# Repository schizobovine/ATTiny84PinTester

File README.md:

# ATTiny84PinTester
Hardware and firmware to test the ATTiny84 series of chips to make sure all GPIOs are working (i.e., I haven't fried them from ESD or a cat peeing on them or whatever).

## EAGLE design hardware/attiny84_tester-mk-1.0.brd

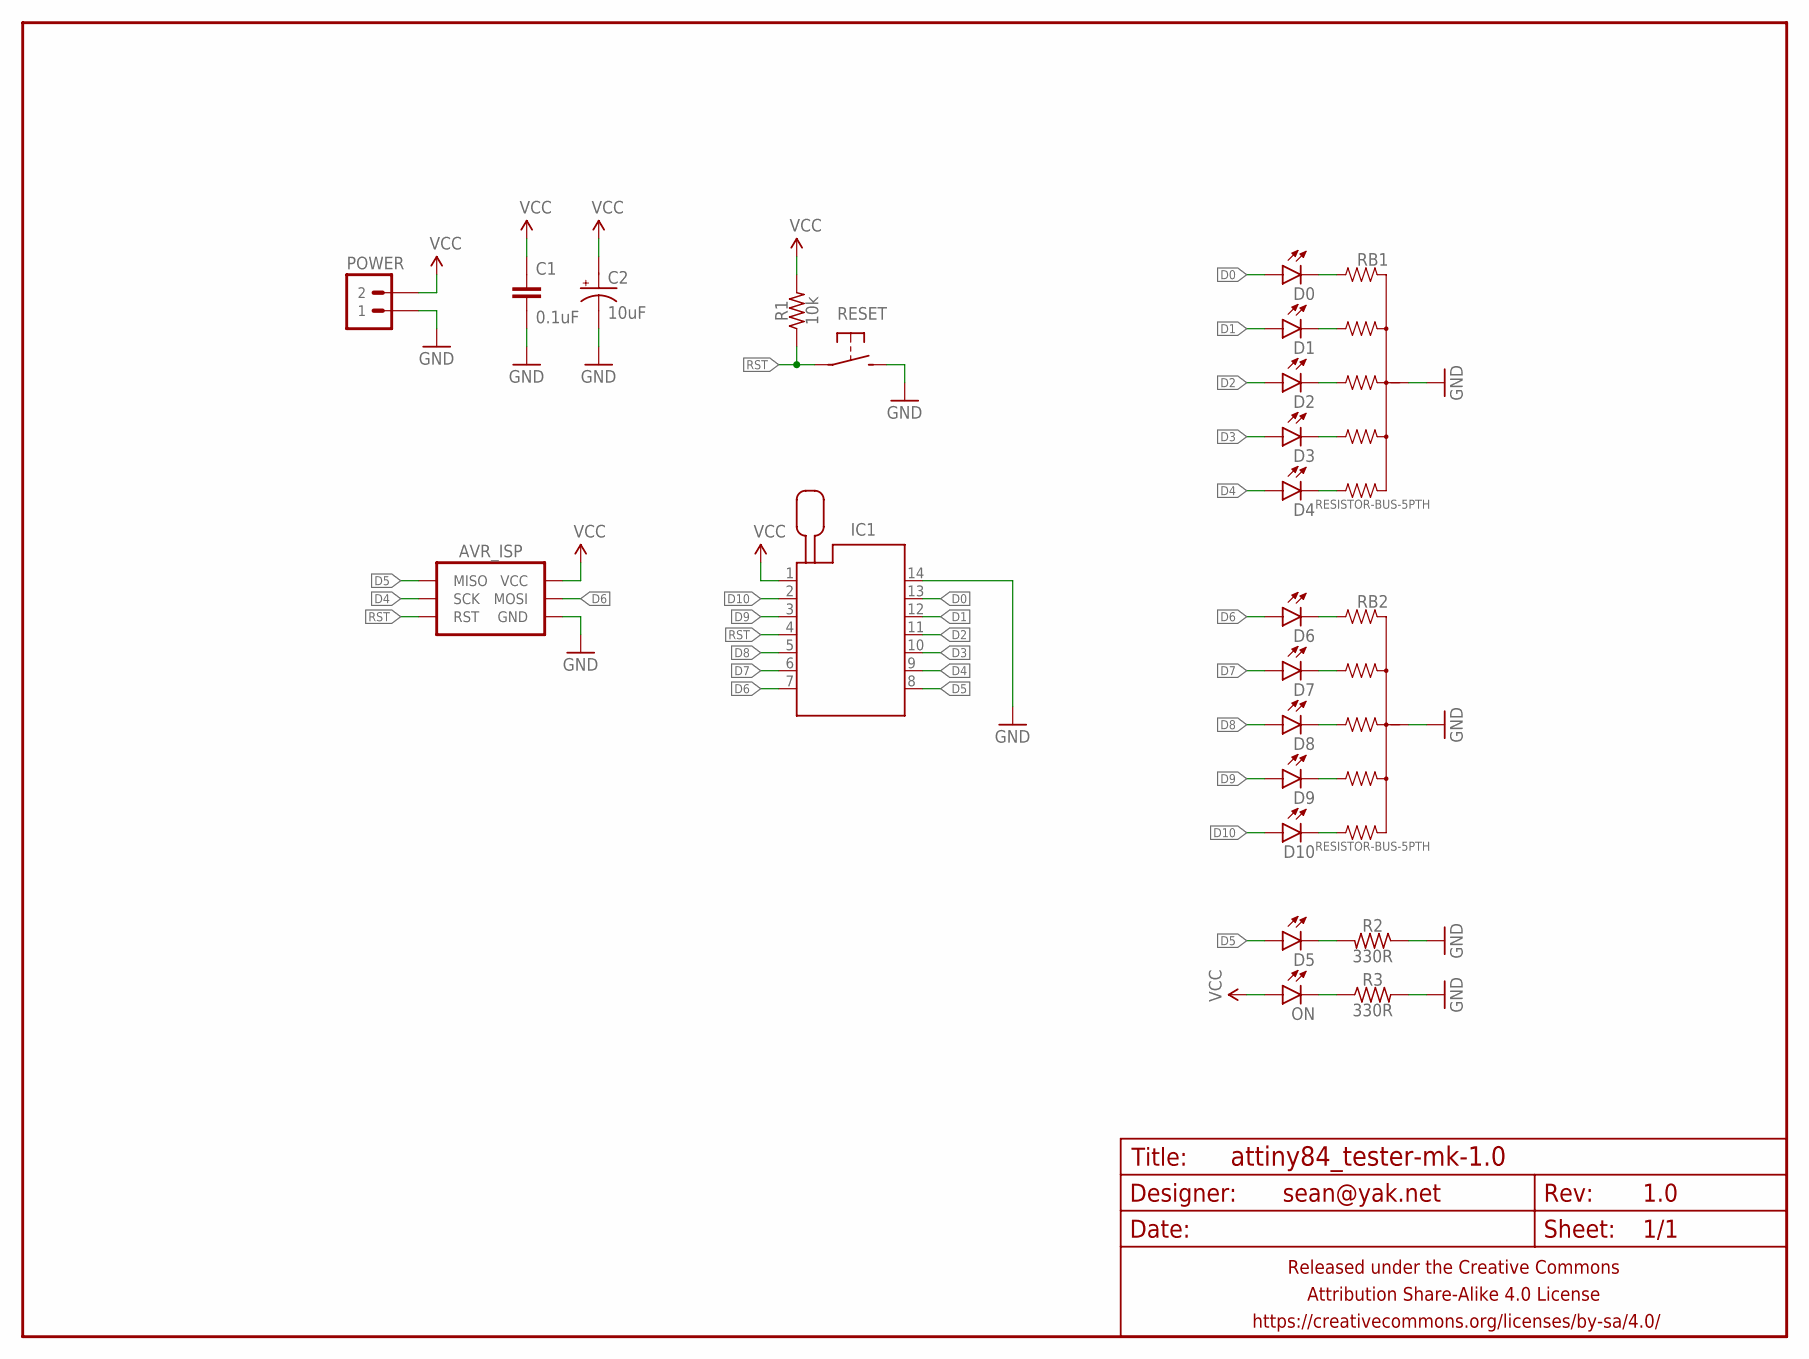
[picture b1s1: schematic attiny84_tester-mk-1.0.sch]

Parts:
AVR_ISP: AVR_SPI_PRG_6PTH-SHROUD; 2X3-SHROUDED
C1: 0.1uF; C025-024X044
C2: 10uF; E2-5
D0, D1, D2, D3, D4, D5, D6, D7, D8, D9, D10: LED3MM-LESS; LED3MM-LESSSILK
FRAME1: FRAME-LETTERNO_PACKAGE; DUMMY
IC1: ATTiny84; ZIF14
ON: LED3MM-LESS; LED3MM-LESSSILK
POWER: M02PTH-CENTERED-R+; 1X02-CENTER-R+
R1: 10k; RESISTOR-AXIAL-PTH-5.08MM
R2, R3: 330R; RESISTOR-AXIAL-PTH-5.08MM
RB1, RB2: RESISTOR-BUS-5PTH; 1X06
RESET: SPST-NO-TACT6MM-PTH-SMALL-PADS; DTS-6-SMALL-PADS

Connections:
D0: D0.A, IC1.13
D1: D1.A, IC1.12
D2: D2.A, IC1.11
D3: D3.A, IC1.10
D4: AVR_ISP.3 (SCK), D4.A, IC1.9
D5: AVR_ISP.1 (MISO), D5.A, IC1.8
D6: AVR_ISP.4 (MOSI), D6.A, IC1.7
D7: D7.A, IC1.6
D8: D8.A, IC1.5
D9: D9.A, IC1.3
D10: D10.A, IC1.2
GND: AVR_ISP.6 (GND), C1.2, C2.-, IC1.14, POWER.1, R2.P$1 (1), R3.P$2 (2), RB1.6 (COM), RB2.6 (COM), RESET.3 (2), RESET.4 (2)
unnamed: ON.K (C), R3.P$1 (1)
unnamed: D0.K (C), RB1.1
unnamed: D1.K (C), RB1.2
unnamed: D2.K (C), RB1.3
unnamed: D3.K (C), RB1.4
unnamed: D4.K (C), RB1.5
unnamed: D5.K (C), R2.P$2 (2)
unnamed: D6.K (C), RB2.1
unnamed: D7.K (C), RB2.2
unnamed: D8.K (C), RB2.3
unnamed: D9.K (C), RB2.4
unnamed: D10.K (C), RB2.5
RST: AVR_ISP.5 (RST), IC1.4, R1.P$1 (1), RESET.1, RESET.2 (1)
VCC: AVR_ISP.2 (VCC), C1.1, C2.+, IC1.1, ON.A, POWER.2, R1.P$2 (2)

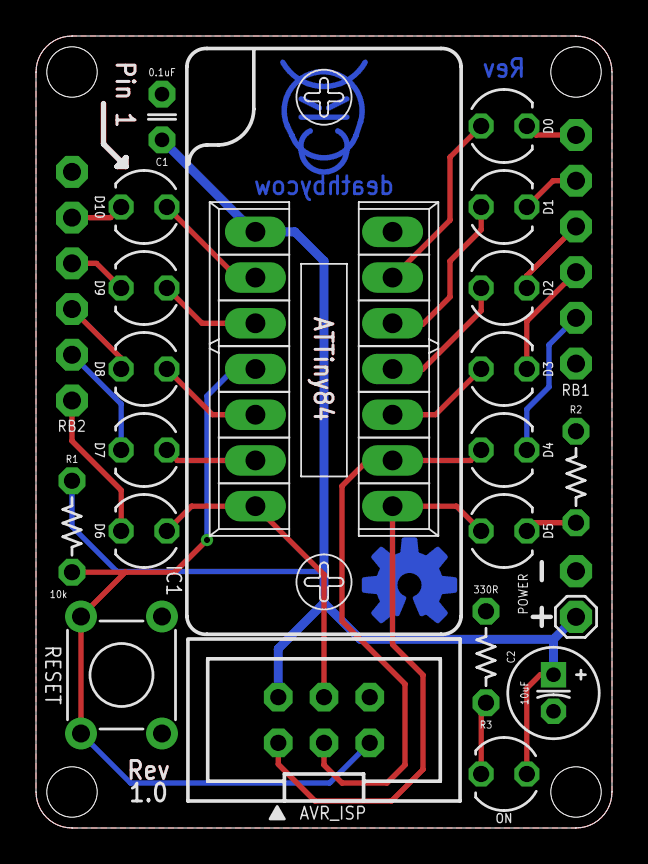
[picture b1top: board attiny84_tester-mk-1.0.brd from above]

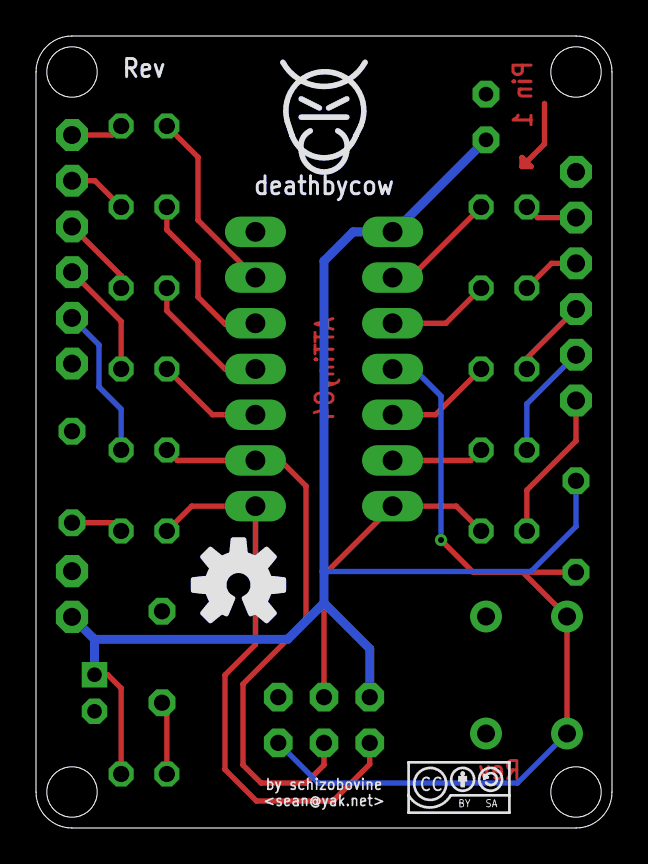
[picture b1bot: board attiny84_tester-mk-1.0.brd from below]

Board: 2 copper layers, 32.0 x 44.0 mm, 27 parts (2 on the bottom side), 26 nets.

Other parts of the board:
U$1: COW_SMALL_METAL
U$2: CC-BY-SA-4.0-NO-URL
U$3: OSHWLOGO_BOT_0.2_A

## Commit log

2015-04-19 initial checkin
2015-04-19 removing spurious backup file
2015-04-19 add ignore to keep that sorta crap out
2015-04-19 flopped tValues to tPlace so OSHPark will put it on the silkscreen. added github link to description
2015-04-19 and now add in revision info since i'm bound to want that later
2015-04-19 changed names to be more helpful
2015-04-20 this shouldn't be here

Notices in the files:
parts and their libraries:
A_butts: Released under the Creative Commons Attribution Share-Alike 4.0 License
A_butts: https://creativecommons.org/licenses/by-sa/4.0
A_butts: Released under the Creative Commons
